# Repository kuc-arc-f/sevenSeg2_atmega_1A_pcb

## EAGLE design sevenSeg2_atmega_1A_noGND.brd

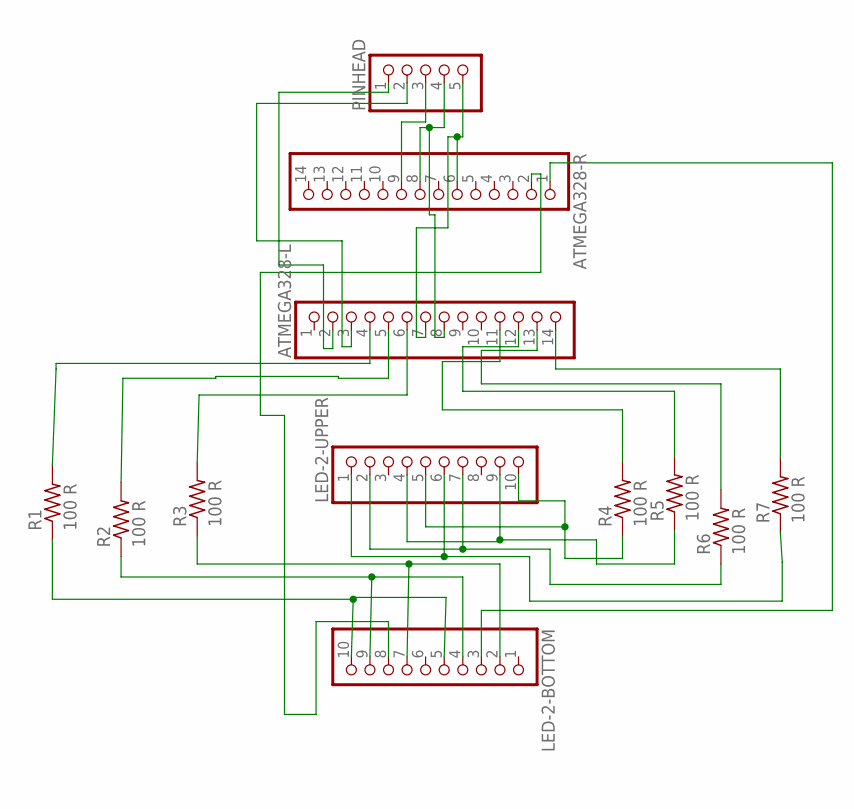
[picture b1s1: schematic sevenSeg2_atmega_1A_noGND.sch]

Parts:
ATMEGA328-L, ATMEGA328-R: PINHD-1X14; 1X14
LED-2-BOTTOM, LED-2-UPPER: PINHD-1X10; 1X10
PINHEAD: PINHD-1X5; 1X05
R1, R2, R3, R4, R5, R6, R7: 100 R; 0204/7

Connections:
unnamed: ATMEGA328-R.9, PINHEAD.3
unnamed: ATMEGA328-L.2, PINHEAD.1
unnamed: ATMEGA328-L.3, PINHEAD.2
unnamed: ATMEGA328-L.8, ATMEGA328-R.8, PINHEAD.4
unnamed: ATMEGA328-L.7, ATMEGA328-R.6, PINHEAD.5
unnamed: ATMEGA328-L.4, R1.2
unnamed: LED-2-BOTTOM.5, LED-2-BOTTOM.10, R1.1
unnamed: ATMEGA328-L.5, R2.2
unnamed: LED-2-BOTTOM.4, LED-2-BOTTOM.9, R2.1
unnamed: ATMEGA328-L.6, R3.2
unnamed: LED-2-BOTTOM.2, LED-2-BOTTOM.7, R3.1
unnamed: ATMEGA328-L.11, R4.2
unnamed: LED-2-UPPER.5, LED-2-UPPER.10, R4.1
unnamed: ATMEGA328-L.12, R5.2
unnamed: LED-2-UPPER.4, LED-2-UPPER.9, R5.1
unnamed: ATMEGA328-L.13, R6.2
unnamed: LED-2-UPPER.2, LED-2-UPPER.7, R6.1
unnamed: ATMEGA328-L.14, R7.2
unnamed: LED-2-UPPER.1, LED-2-UPPER.6, R7.1
unnamed: ATMEGA328-R.2, LED-2-BOTTOM.8
unnamed: ATMEGA328-R.1, LED-2-BOTTOM.3

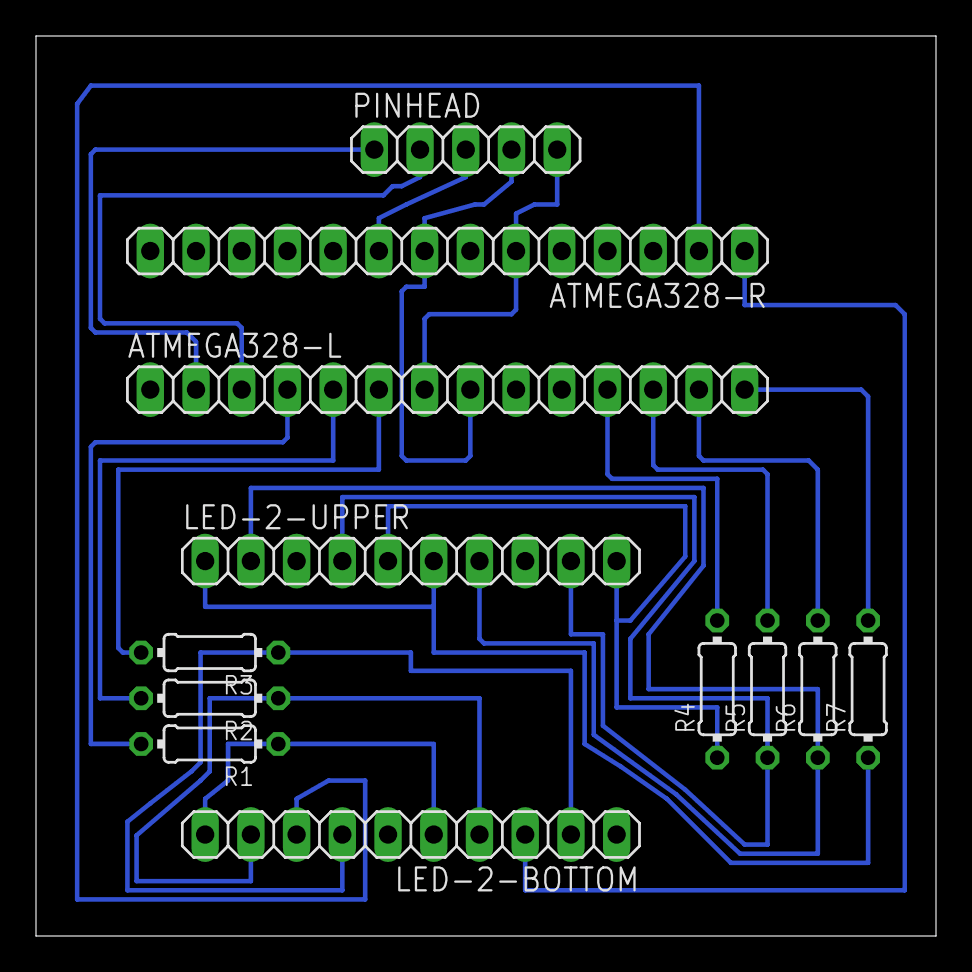
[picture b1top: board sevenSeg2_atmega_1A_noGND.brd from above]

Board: 2 copper layers, 50.0 x 50.0 mm, 12 parts (0 on the bottom side), 21 nets.

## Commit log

2017-08-17 new, 08-17a1
